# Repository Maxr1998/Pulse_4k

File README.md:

# Pulse 4k Macropad

CAD files for plate and PCB of my Pulse 4k macropad, with 4 keys and 2 rotary encoders.

## License

All files in the repository are licensed under a [Creative Commons Attribution-ShareAlike 4.0 International License](http://creativecommons.org/licenses/by-sa/4.0/).

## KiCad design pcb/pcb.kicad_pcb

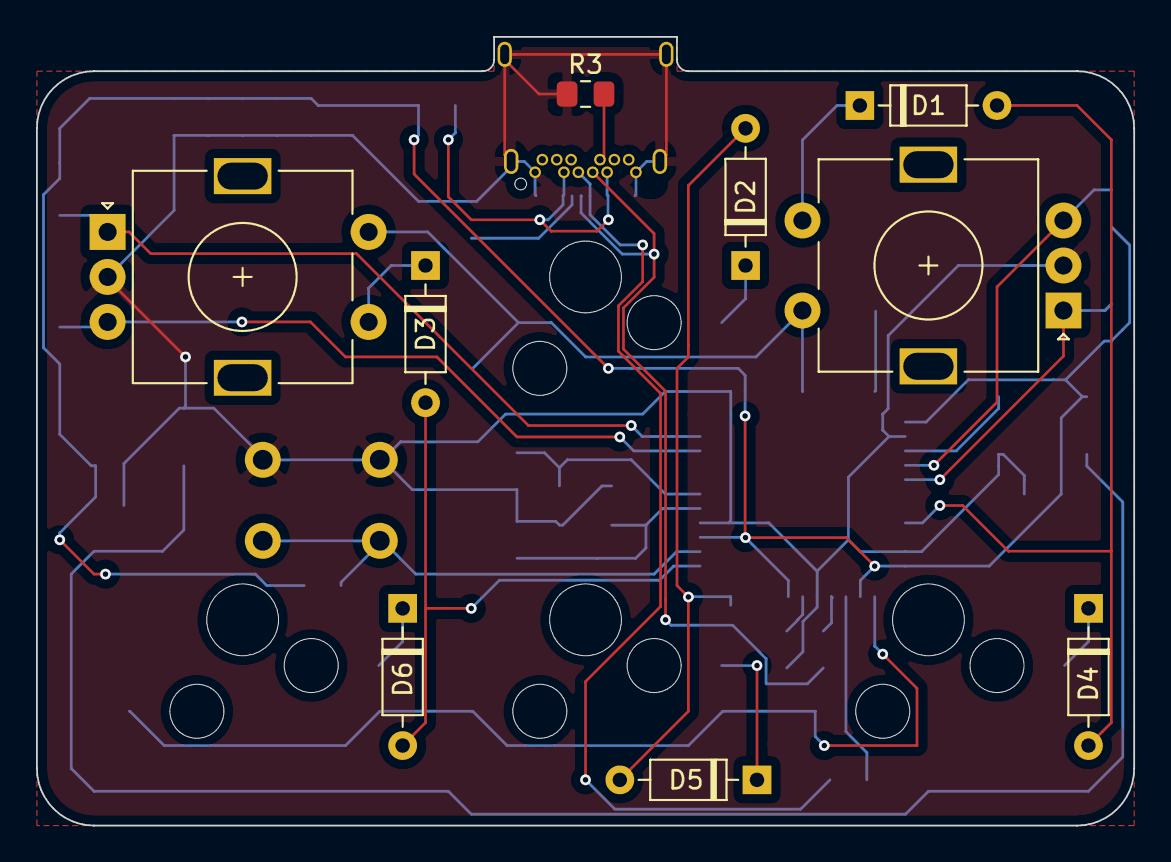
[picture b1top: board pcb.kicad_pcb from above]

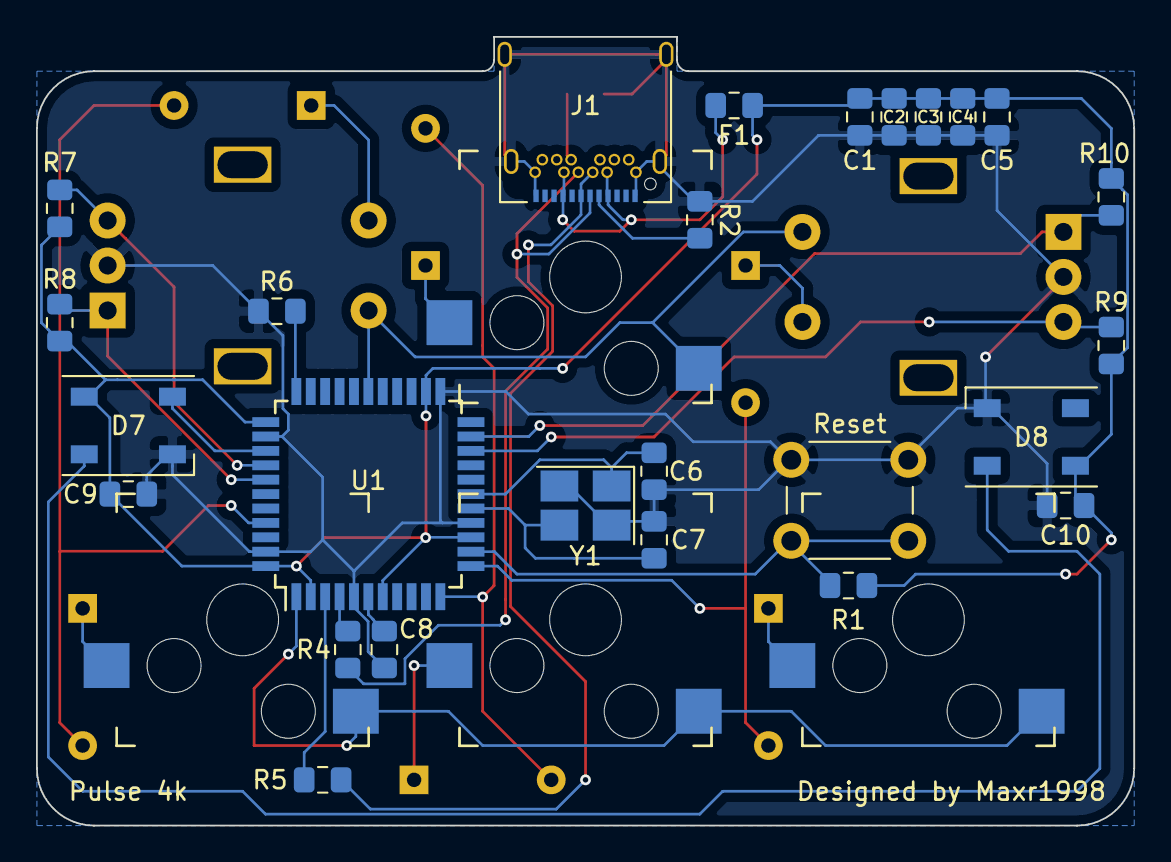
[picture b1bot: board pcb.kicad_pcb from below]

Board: 2 copper layers, 61.0 x 43.8 mm, 39 parts (26 on the bottom side), 31 nets.

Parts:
C1, C2, C3, C4: 0.1uF; C_0805_2012Metric_Pad1.15x1.40mm_HandSolder
C5: 4.7uF; C_0805_2012Metric_Pad1.15x1.40mm_HandSolder
C6, C7: 22pF; C_0805_2012Metric_Pad1.15x1.40mm_HandSolder
C8: 1uF; C_0805_2012Metric_Pad1.15x1.40mm_HandSolder
C9, C10: 100nF; C_0805_2012Metric_Pad1.15x1.40mm_HandSolder
D1, D2, D3, D4, D5, D6: 1N4148; D_DO-35_SOD27_P7.62mm_Horizontal
D7, D8: WS2812B; LED_WS2812B_PLCC4_5.0x5.0mm_P3.2mm
F1: 500mA; Fuse_0805_2012Metric_Pad1.15x1.40mm_HandSolder
J1: USB_C_Receptacle_USB2.0; USB_C_Receptacle_Amphenol_12401548E4-2A
R1, R6, R7, R8, R9, R10: 10k; R_0805_2012Metric_Pad1.15x1.40mm_HandSolder
R2, R3: 5.1k; R_0805_2012Metric_Pad1.15x1.40mm_HandSolder
R4, R5: 22; R_0805_2012Metric_Pad1.15x1.40mm_HandSolder
Reset: Reset; SW_PUSH_6mm
SW2, SW3: EC11; RotaryEncoder_Alps_EC11E-Switch_Vertical_H20mm
SW4, SW5, SW6, SW7: SW_Push; Kailh_socket_plate_mount
U1: ATmega32U4-AU; TQFP-44_10x10mm_P0.8mm
Y1: TSX3225; Crystal_SMD_SeikoEpson_TSX3225-4Pin_3.2x2.5mm_HandSoldering

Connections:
GND: C1.2, C2.2, C3.2, C4.2, C5.2, C6.1, C7.2, C8.2, C9.2, C10.2, D7.3, D8.3, J1.A1, J1.A12, J1.B1, J1.B12, J1.S1, R2.1, R3.1, R6.1, Reset.1, SW2.C, SW3.C, U1.5, U1.15, U1.23, U1.35, U1.43, Y1.2, Y1.4
unnamed: C6.2, U1.17, Y1.1
unnamed: C7.1, U1.16, Y1.3
unnamed: C8.1, U1.6
unnamed: D1.1, SW2.S1
unnamed: D2.1, SW4.2
unnamed: D3.1, SW3.S1
unnamed: D4.1, SW5.2
unnamed: D5.1, SW6.2
unnamed: D6.1, SW7.2
unnamed: D7.2, D8.4
unnamed: J1.A5, R2.2
unnamed: J1.A6, J1.B6, R4.2
unnamed: J1.A7, J1.B7, R5.2
unnamed: J1.B5, R3.2
unnamed: R1.1, Reset.2, U1.13
unnamed: R4.1, U1.4
unnamed: R5.1, U1.3
unnamed: R6.2, U1.33
R1A: R8.2, SW2.A, U1.38
R1B: R7.1, SW2.B, U1.37
R2A: R10.2, SW3.A, U1.21
R2B: R9.1, SW3.B, U1.20
VBUS: F1.2, J1.A4, J1.A9, J1.B4, J1.B9
VCC: C1.1, C2.1, C3.1, C4.1, C5.1, C9.1, C10.1, D7.1, D8.1, F1.1, R1.2, R7.2, R8.1, R9.2, R10.1, U1.2, U1.7, U1.14, U1.24, U1.34, U1.44
col0: D1.2, D4.2, U1.41
col1: D2.2, D5.2, U1.11
col2: D3.2, D6.2, U1.12
led0: D7.4, U1.36
row0: SW2.S2, SW3.S2, SW4.1, U1.28
row1: SW5.1, SW6.1, SW7.1, U1.1

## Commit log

2019-05-02 Initial
2019-05-02 Finish PCB design, generate gerber files
